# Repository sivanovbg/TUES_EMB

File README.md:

GitHub repo for TUES grade 11 projects to use in students' embedded coureses

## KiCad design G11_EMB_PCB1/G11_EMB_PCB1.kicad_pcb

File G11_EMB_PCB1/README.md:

**TUES G11 EMB PCB1 is a Power supply units (PSU) Demo board version 1 (v1)**

It covers three types of DC/DC convertsrs:

1. UCC12050 - insolated input to output DC/DC converter
2. LM1117R-ADJ - Linear DC/DC converter
3. SY8089AAAC - Switching DC/DC converter

**Enjoy!**

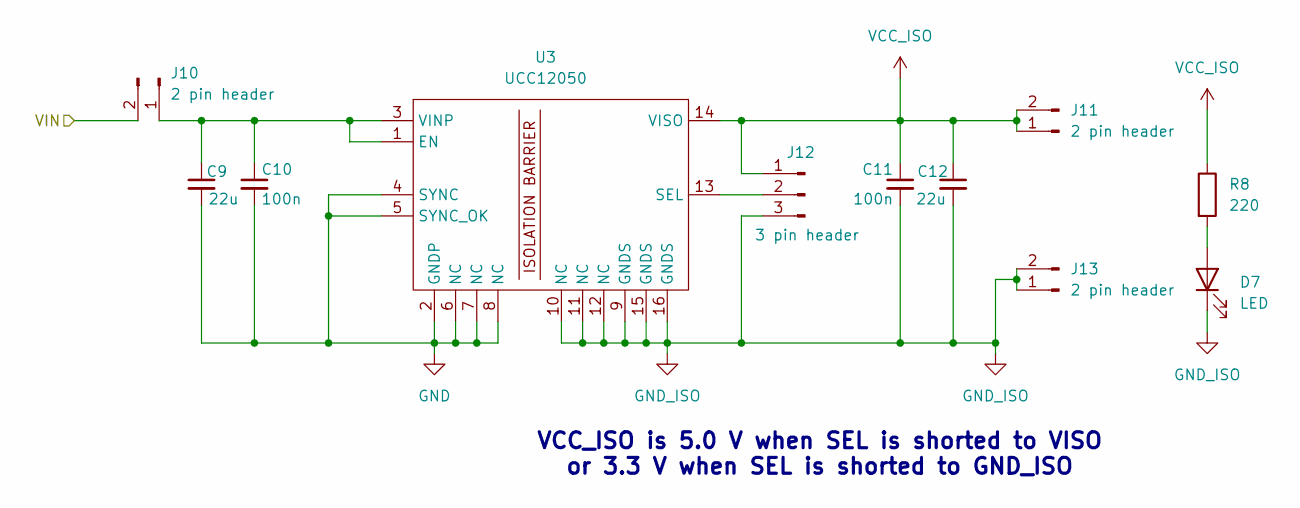
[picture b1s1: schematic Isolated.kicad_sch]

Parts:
C9, C12: 22u; C_0603_1608Metric_Pad1.08x0.95mm_HandSolder
C10, C11: 100n; C_0603_1608Metric_Pad1.08x0.95mm_HandSolder
D7: LED; LED_0603_1608Metric_Pad1.05x0.95mm_HandSolder
J10, J11, J13: 2 pin header; PinSocket_1x02_P2.54mm_Vertical
J12: 3 pin header; PinHeader_1x03_P2.54mm_Vertical
R8: 220; R_0603_1608Metric_Pad0.98x0.95mm_HandSolder
U3: UCC12050; SOIC-16_UCC12050

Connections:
GND: C9.2, C10.2, U3.2 (GNDP), U3.4 (SYNC), U3.5 (SYNC_OK), U3.6 (NC), U3.7 (NC), U3.8 (NC); also elsewhere on the board
GND_ISO: C11.2, C12.2, D7.1 (K), J12.3, J13.1, J13.2, U3.9 (GNDS), U3.10 (NC), U3.11 (NC), U3.12 (NC), U3.15 (GNDS), U3.16 (GNDS)
unnamed: D7.2 (A), R8.2
unnamed: C9.1, C10.1, J10.1, U3.1 (EN), U3.3 (VINP)
unnamed: J12.2, U3.13 (SEL)
VCC_ISO: C11.1, C12.1, J11.1, J11.2, J12.1, R8.1, U3.14 (VISO)
VIN: J10.2; also elsewhere on the board

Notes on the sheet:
VCC_ISO is 5.0 V when SEL is shorted to VISO or 3.3 V when SEL is shorted to GND_ISO

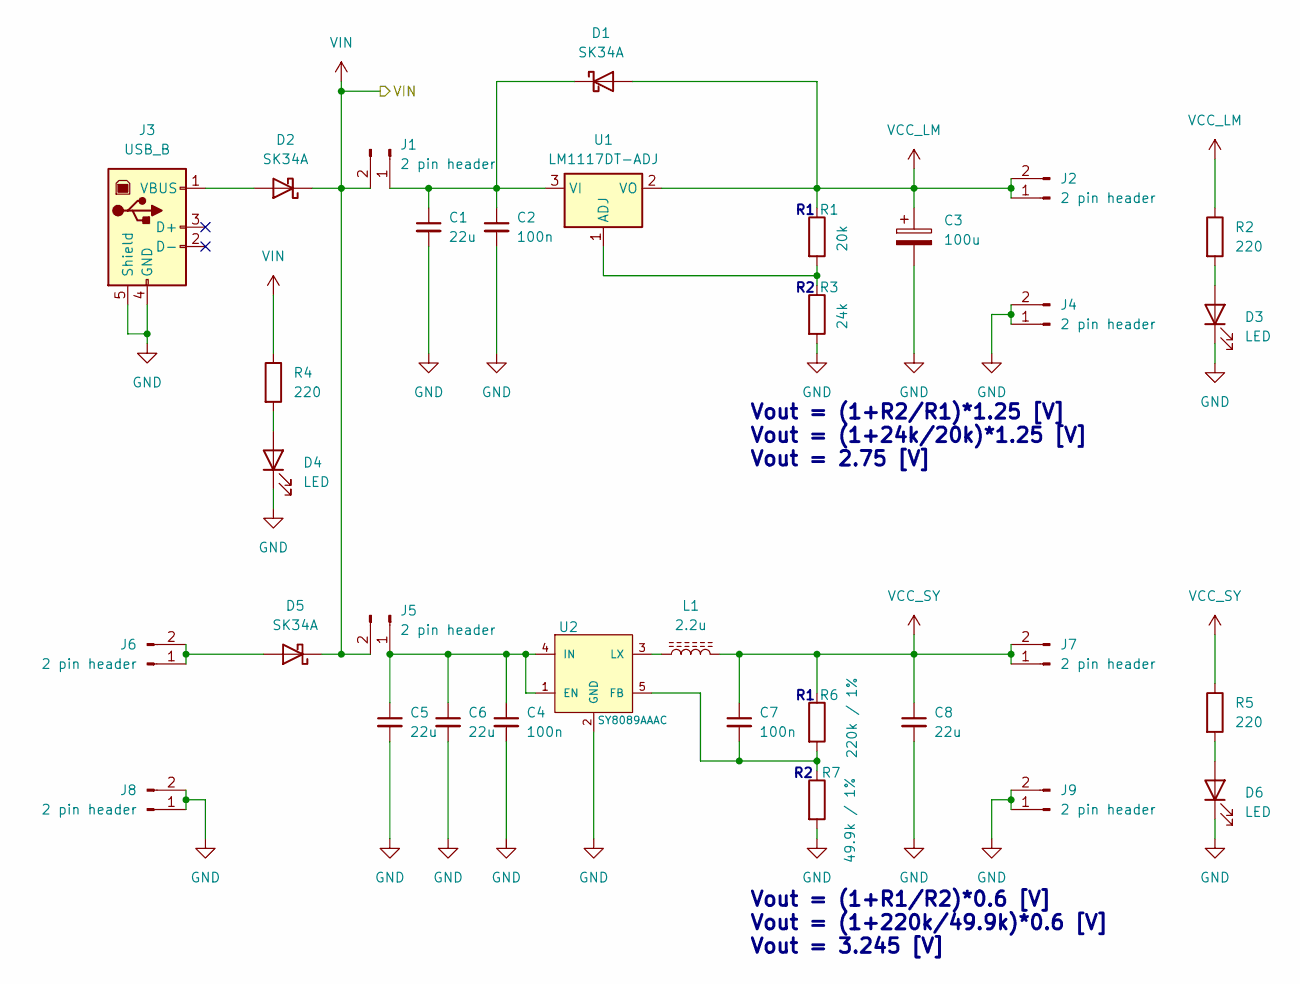
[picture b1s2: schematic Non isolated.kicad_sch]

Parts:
C1, C5, C6, C8: 22u; C_0603_1608Metric_Pad1.08x0.95mm_HandSolder
C2, C4, C7: 100n; C_0603_1608Metric_Pad1.08x0.95mm_HandSolder
C3: 100u; CP_EIA-7343-31_Kemet-D
D1, D2, D5: SK34A; D_SMA_Handsoldering
D3, D4, D6: LED; LED_0603_1608Metric_Pad1.05x0.95mm_HandSolder
J1, J2, J4, J5, J6, J7, J8, J9: 2 pin header; PinSocket_1x02_P2.54mm_Vertical
J3: USB_B; USB_B_Lumberg_2411_02_Horizontal
L1: 2.2u; L_Coilcraft_XxL4020
R1: 20k; R_0603_1608Metric_Pad0.98x0.95mm_HandSolder
R2, R4, R5: 220; R_0603_1608Metric_Pad0.98x0.95mm_HandSolder
R3: 24k; R_0603_1608Metric_Pad0.98x0.95mm_HandSolder
R6: 220k / 1%; R_0603_1608Metric_Pad0.98x0.95mm_HandSolder
R7: 49.9k / 1%; R_0603_1608Metric_Pad0.98x0.95mm_HandSolder
U1: LM1117DT-ADJ; TO-252-2
U2: SY8089AAAC; SOT-23-5_HandSoldering

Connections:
GND: C1.2, C2.2, C3.2, C4.2, C5.2, C6.2, C8.2, D3.1 (K), D4.1 (K), D6.1 (K), J3.4 (GND), J3.5 (Shield), J4.1, J4.2, J8.1, J8.2, J9.1, J9.2, R3.2, R7.2, U2.2 (GND); also elsewhere on the board
unnamed: C1.1, C2.1, D1.1 (K), J1.1, U1.3 (VI)
unnamed: D2.2 (A), J3.1 (VBUS)
unnamed: D3.2 (A), R2.2
unnamed: D4.2 (A), R4.2
unnamed: D5.2 (A), J6.1, J6.2
unnamed: D6.2 (A), R5.2
unnamed: C4.1, C5.1, C6.1, J5.1, U2.1 (EN), U2.4 (IN)
unnamed: R1.2, R3.1, U1.1 (ADJ)
unnamed: C7.2, R6.2, R7.1, U2.5 (FB)
unnamed: L1.1, U2.3 (LX)
VCC_LM: C3.1, D1.2 (A), J2.1, J2.2, R1.1, R2.1, U1.2 (VO)
VCC_SY: C7.1, C8.1, J7.1, J7.2, L1.2, R5.1, R6.1
VIN: D2.1 (K), D5.1 (K), J1.2, J5.2, R4.1; also elsewhere on the board

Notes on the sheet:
Vout = (1+R2/R1)*1.25 [V] Vout = (1+24k/20k)*1.25 [V] Vout = 2.75 [V]
Vout = (1+R1/R2)*0.6 [V] Vout = (1+220k/49.9k)*0.6 [V] Vout = 3.245 [V]

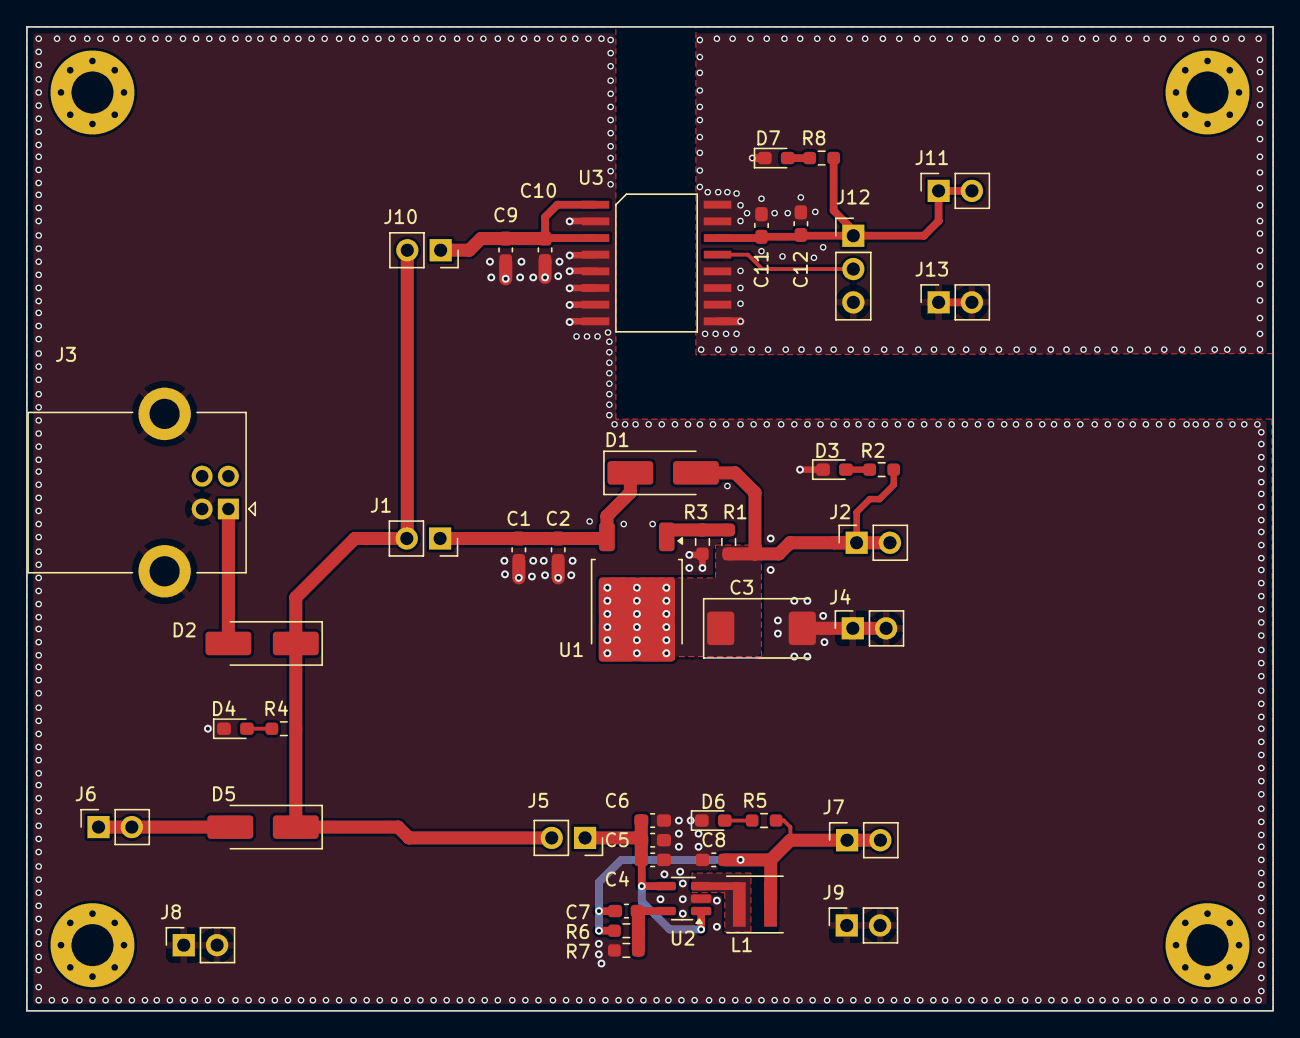
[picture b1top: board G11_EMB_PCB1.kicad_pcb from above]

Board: 2 copper layers, 95.0 x 75.0 mm, 44 parts (0 on the bottom side), 19 nets.

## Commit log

2024-10-02 2024-10-02
2024-10-03 2024-10-03 M
2024-10-03 2024-10-03
2024-10-05 2024-10-04
